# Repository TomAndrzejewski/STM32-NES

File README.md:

# STM32-NES
NES games emulator on STM32

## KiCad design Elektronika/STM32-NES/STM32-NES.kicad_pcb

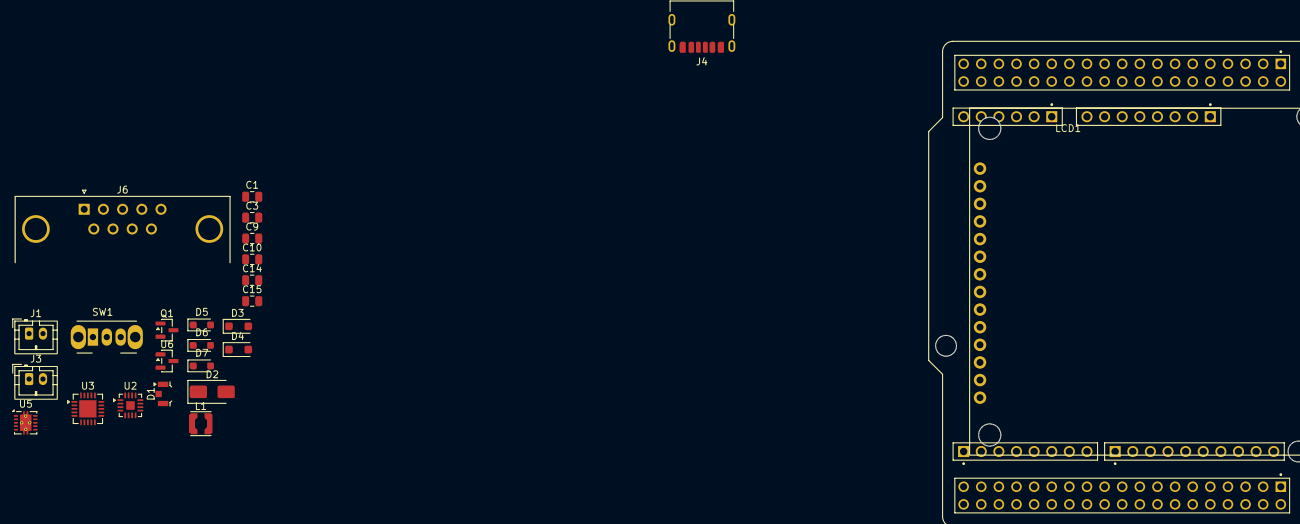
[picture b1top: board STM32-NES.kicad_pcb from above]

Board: 2 copper layers, 26 parts (0 on the bottom side), 25 nets, no tracks yet.

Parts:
C1, C9, C10, C14: 10u; C_0805_2012Metric
C3: 4u7; C_0805_2012Metric
C15: 100n; C_0805_2012Metric
D1: LTST-S326KGJRKT; LED_LiteOn_LTST-S326
D2: SMAJ5.0A; D_SMA
D3, D4: SMF5.0A; D_SOD-123F
D5, D6, D7: SZESD7351HT1G; D_SOD-323_HandSoldering
J1: BATT; JST_PH_B2B-PH-K_1x02_P2.00mm_Vertical
J3: Speaker; JST_PH_B2B-PH-K_1x02_P2.00mm_Vertical
J4: USB4125-GF-A; USB_C_Receptacle_HRO_TYPE-C-31-M-17
J6: DE09-PL-24; DSUB-9_Pins_Horizontal_P2.77x2.84mm_EdgePinOffset4.94mm_Hou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
L1: DJNR3015-2R2; L_Coilcraft_LPS3010
LCD1: TFT 2.8' ST7789V
Q1: 2N7002; SOT-23
SW1: OS102011MA1QN1C; SW_Slide_SPDT_Angled_CK_OS102011MA1Q
U1: NUCLEO-F446RE; MODULE_NUCLEO-F446RE
U2: MAX98357A; TQFN-16-1EP_3x3mm_P0.5mm_EP1.23x1.23mm
U3: MCP73871-2CC; QFN-20-1EP_4x4mm_P0.5mm_EP2.5x2.5mm
U5: TPS63002; Texas_DRC0010J_ThermalVias
U6: AZ431AN-ATRE1; SOT-23

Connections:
+3.3V: J6.6, LCD1.8 (LED), U1.CN7_16 (CN7_+3V3)
+5V: C9.1, C10.1, C14.1, C15.1, LCD1.1 (VCC), U1.CN7_6 (E5V), U2.2 (GAIN_SLOT), U2.7 (VDD), U2.8 (VDD), U5.1 (VOUT), U5.10 (FB)
+BATT: J1.2, U3.14 (V_{BAT}), U3.15 (V_{BAT}), U3.16 (V_{BAT_SENSE})
/CLK: D7.1 (A1_1), U1.CN10_33 (PA10)
/CS: LCD1.3 (CS), U1.CN7_32 (PA4)
/DATA: D5.1 (A1), U1.CN10_25 (PB10)
/DC: LCD1.5 (DC), U1.CN7_30 (PA1)
/LATCH: D6.1 (A1), U1.CN10_29 (PB5)
/MISO: LCD1.9 (SDO(MISO)), U1.CN10_13 (PA6)
/MOSI: LCD1.6 (SDI(MOSI)), U1.CN10_15 (PA7)
/RESET: LCD1.4 (RESET), U1.CN7_28 (PA0)
/SCK: LCD1.7 (SCK), U1.CN10_11 (PA5)
/VBAT/5V do przewornicy: C3.1, U3.1 (OUT), U3.20 (OUT), U5.5 (VIN)
CN10_GND: U1.CN10_9 (CN10_GND), U1.CN10_20 (CN10_GND)
GND: C1.2, C3.2, C9.2, C10.2, C14.2, C15.2, D2.2 (A2), D3.2 (A2), D4.2 (A2), D5.2 (A2), D6.2 (A2), J1.1, J4.A12 (GND), J4.B12 (GND), J4.SH (SHIELD), J6.8, J6.SH (PAD), LCD1.2 (GND), Q1.2 (S), SW1.1 (A), U1.CN7_8 (CN7_GND), U1.CN7_19 (CN7_GND), U1.CN7_20 (CN7_GND), U1.CN7_22 (CN7_GND), U2.3 (GND), U2.11 (GND), U2.15 (GND), U2.17 (PAD), U3.10 (V_{SS}), U3.11 (V_{SS}), U3.21 (V_{SS}), U5.3 (PGND), U5.9 (GND), U5.11 (PGND), U6.3 (A)
unnamed: D3.1 (A1), J4.B5 (CC2)
unnamed: D4.1 (A1), J4.A5 (CC1)
unnamed: J3.1, U2.9 (OUTP)
unnamed: J3.2, U2.10 (OUTN)
unnamed: Q1.3 (D), U3.3 (SEL)
unnamed: SW1.2 (B), U5.6 (EN), U5.7 (PS/SYNC), U5.8 (VINA)
unnamed: L1.1, U5.4 (L1)
unnamed: L1.2, U5.2 (L2)
unnamed: U6.1 (REF), U6.2 (K)
VBUS: C1.1, D1.3 (A), D2.1 (A1), J4.A9 (VBUS), J4.B9 (VBUS), U3.2 (VPCC), U3.4 (PROG2), U3.17 (CE), U3.18 (IN), U3.19 (IN)

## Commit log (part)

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2026-05-07 First commit with source code and config
2026-05-07 Sysclk changed to 144MHz
2026-05-19 Added basic communication with LCD via SPI, tested SPI+DMA
2026-05-20 First mario bitmap rendered :D
2026-05-31 Fake NES Pad control programmed and tested.
2026-06-04 Renderowanie Mario na bazie DirtyRectangles
2026-06-05 Cleanup of main, moved logic to Mario.c
2026-06-08 First background render, test of vertical scroll functionality.
2026-06-11 Partial sprite render based on visibility
2026-06-12 Zrzut co zrobilem wczoraj
2026-06-12 Dopisane notatki
2026-06-12 Będziemy renderować prostokąty po scrollu
2026-06-12 Nie mam wiecej pomyslu
2026-06-13 Zmiana logiki renderowania na dwówymiarową tablicę. Działa ucinanie spritów. Dodatkowe makro dla optymalizacji nieoptymalnie napisanych funkcji, żeby w debugu szybciej się wykonywały
2026-06-13 Działa renderowanie konkretnego wycinka z ekranu
2026-06-17 Poprawiono renderowanie konkretnego wycinka ekranu, działa renderowanie pojedyńczych linii na bokach ekranu + scrolling, czyli podstawa optymalizacji! :D
2026-06-17 Renderujemy chmurkę, trochę systematyzacji dla statycznych bitmap. Trzeba wykorzystać jakiś edytor map.
2026-06-28 Automatyzacja backgroundu mapy przy pomocy Tiles. Renderujemy obiekty nad warstwą backgroundu.
2026-06-28 Renderujemy kilka goomb na raz, priorytet renderowania tak aby kontrolować co jest na wierzchu.
2026-06-30 DMA SPI do wyświetlacza jest nieblokujące, obsługa zakończenia DMA w przerwaniu
2026-06-30 Odpalamy timer 60Hz, czeka mnie duże przestawienie na system-based zamiast object-based :D
